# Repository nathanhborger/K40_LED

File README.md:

# K40_LED
LED Ring Origin Light for K40 Laser.
This device was designed with the intention to provide a solution to the K40's lack of origin detection/positioning.
Placed at the back of the laser, and reflected through two mirrors, the light will shine on the working peice, making a very distinct appearance which simplifies and enables the user to identify the exact locatin of the laser head.

## Schematic

## PCB Layout

## PCB

## Parts List
| QTY | PART | NOTES |
|:---:|:----:|:-----:|
|8|LED XLAMP COOL WHITE 5000K 2SMD|https://cree-led.com/media/documents/XLampMX3.pdf|
|13|RES 13 OHM 1% 1/8W 0805||
|4|IC LED DRIVER LIN 1.5A 8SOPWRPAD|https://www.ti.com/general/docs/suppproductinfo.tsp?distId=10&gotoUrl=https%3A%2F%2Fwww.ti.com%2Flit%2Fgpn%2Flm3466|
|1|LED DRIVER CC BUCK 2-52V 350MA|https://www.meanwellusa.com/upload/pdf/LDD-H/LDD-H-spec.pdf|
|4|RES SMD 1 OHM 1% 1/8W 0805||
|4|CAP CER 0.011UF 50V C0G/NP0 0805	||
|5|CAP CER 1UF 16V X7R 0805||
|1|RES SMD 51.1 OHM 1% 1/8W 0805||

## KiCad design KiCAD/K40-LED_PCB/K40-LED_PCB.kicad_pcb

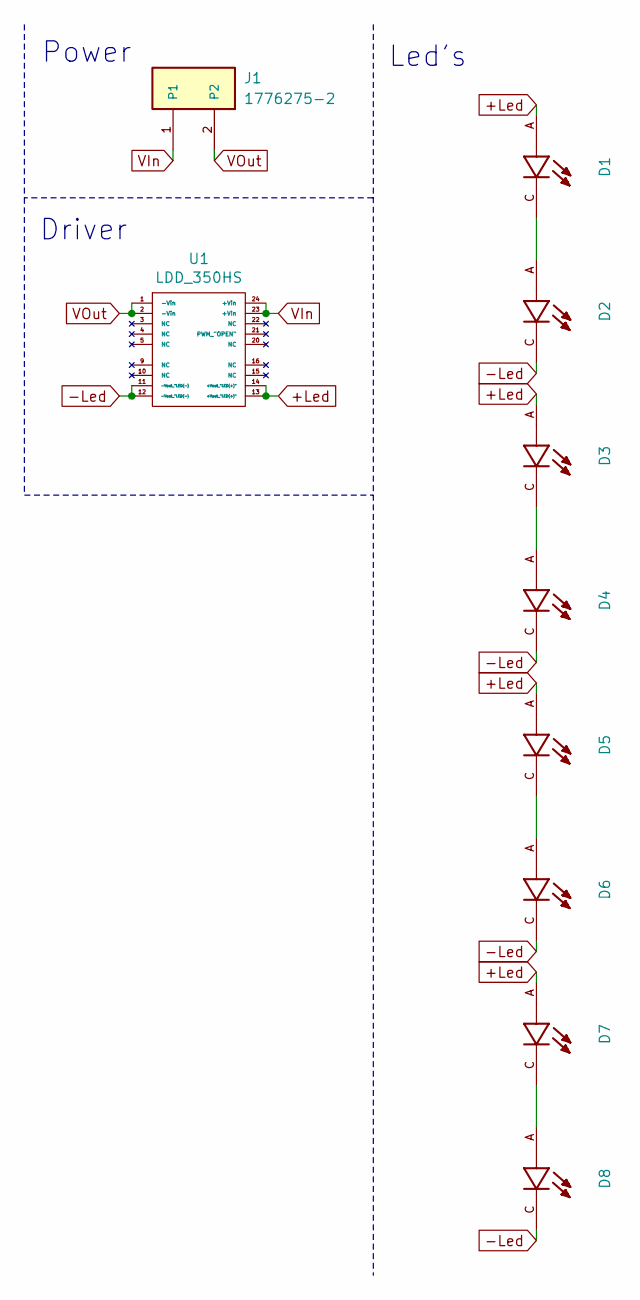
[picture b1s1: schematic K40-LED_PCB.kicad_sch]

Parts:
D1: Cree_MX3AWT-A1-R250-000BE3
D2, D3, D4, D5, D6, D7, D8: LTST-C190KGKT; Cree_MX3AWT-A1-R250-000BE3
J1: 1776275-2; TE_1776275-2; VOLTAGE_RATING_AC 250V; PART_DESCRIPTION TERM BLOCK 2POS SIDE ENT 3.5MM
U1: LDD_350HS; LDD-350HS

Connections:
+Led: D1.A, D3.A, D5.A, D7.A, U1.13 (+Vout_"LED(+)"), U1.14 (+Vout_"LED(+)")
-Led: D2.C, D4.C, D6.C, D8.C, U1.11 (-Vout_"LED(-)), U1.12 (-Vout_"LED(-))
unnamed: D1.C, D2.A
unnamed: D3.C, D4.A
unnamed: D5.C, D6.A
unnamed: D7.C, D8.A
VIn: J1.1, U1.23 (+Vin), U1.24 (+Vin); also elsewhere on the board
VOut: J1.2, U1.1 (-Vin), U1.2 (-Vin)

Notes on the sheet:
Power
Led's
Driver

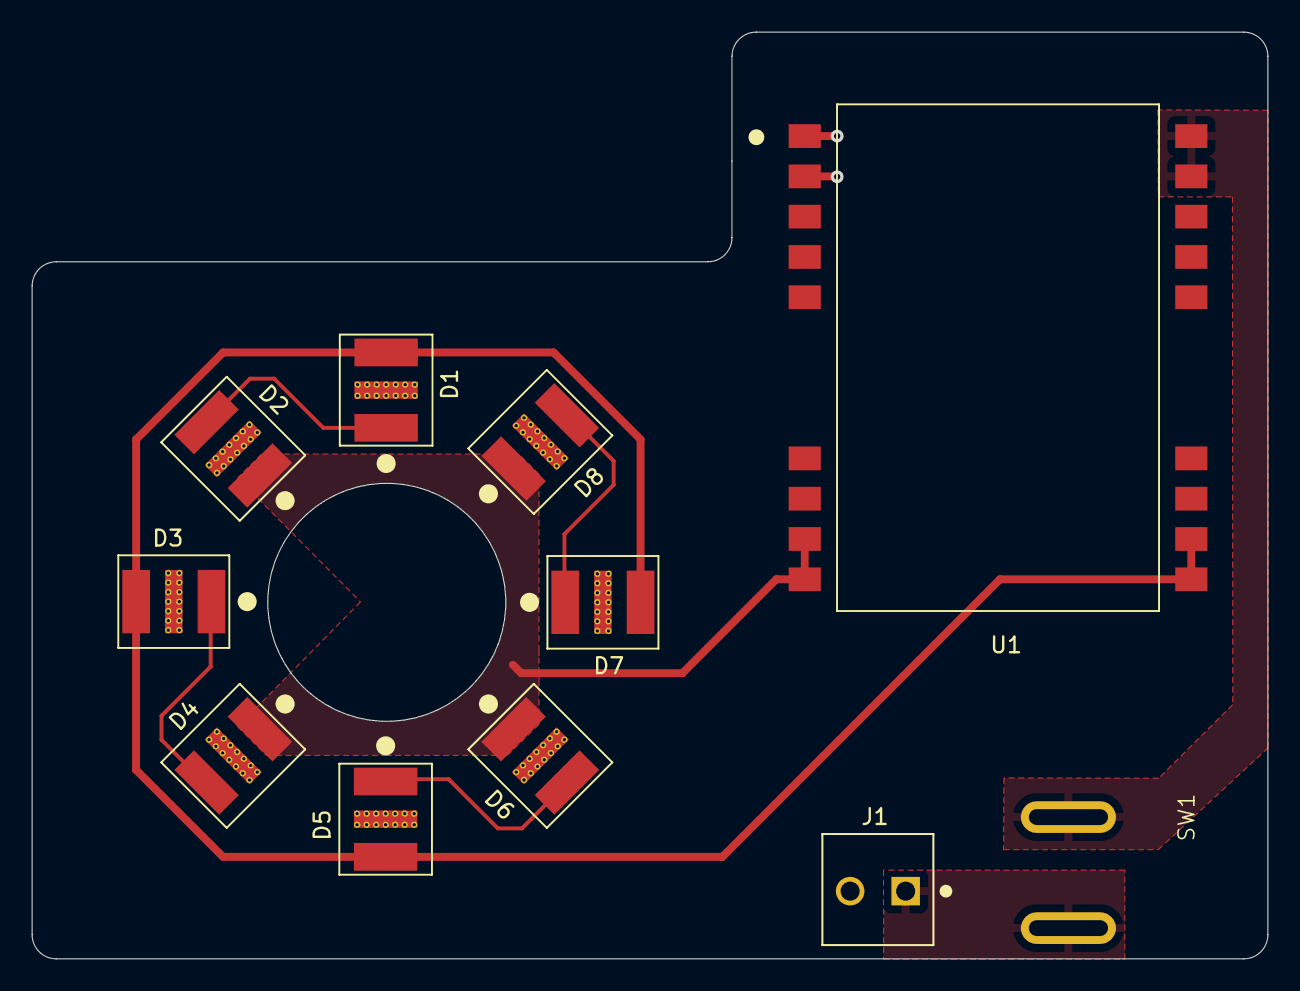
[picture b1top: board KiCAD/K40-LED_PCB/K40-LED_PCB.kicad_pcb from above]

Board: 2 copper layers, 77.9 x 58.4 mm, 11 parts (0 on the bottom side), 8 nets.

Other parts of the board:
SW1: SW_SPST; RA1113112R

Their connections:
VIn: SW1.1 (A), SW1.2 (B); also elsewhere on the board

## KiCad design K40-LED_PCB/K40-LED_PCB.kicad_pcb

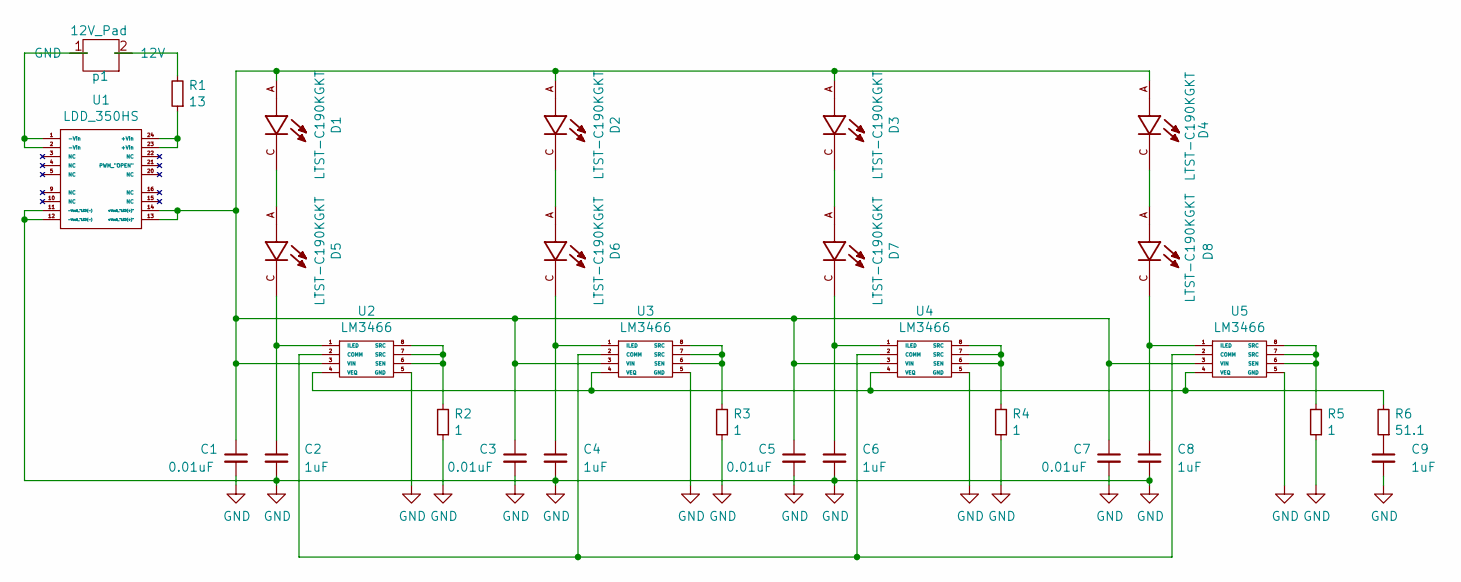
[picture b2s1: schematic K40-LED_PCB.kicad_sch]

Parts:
C1, C3, C5, C7: 0.01uF; C_0805_2012Metric
C2, C4, C6, C8, C9: 1uF; C_0805_2012Metric
D1, D2, D3, D4, D5, D6, D7, D8: LTST-C190KGKT; Cree_MX3AWT-A1-R250-000BE3
R1: 13; R_0805_2012Metric
R2, R3, R4, R5: 1; R_0805_2012Metric
R6: 51.1; R_0805_2012Metric
U1: LDD_350HS; LDD-350HS
U2, U3, U4, U5: LM3466; NOPB
p1: 12V_Pad; 12V_Through_Hole

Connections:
GND: C1.2, C2.2, C3.2, C4.2, C5.2, C6.2, C7.2, C8.2, C9.2, D1.65, D2.65, D3.65, D4.65, D5.65, D6.65, D7.65, D8.65, R2.1, R3.1, R4.1, R5.1, U1.11 (-Vout_"LED(-)), U1.12 (-Vout_"LED(-)), U2.5 (GND), U2.9, U3.5 (GND), U3.9, U4.5 (GND), U4.9, U5.5 (GND), U5.9
unnamed: C1.1, C3.1, C5.1, C7.1, D1.A, D2.A, D3.A, D4.A, U1.13 (+Vout_"LED(+)"), U1.14 (+Vout_"LED(+)"), U2.3 (VIN), U3.3 (VIN), U4.3 (VIN), U5.3 (VIN)
unnamed: C2.1, D5.C, U2.1 (ILED)
unnamed: C4.1, D6.C, U3.1 (ILED)
unnamed: C6.1, D7.C, U4.1 (ILED)
unnamed: C8.1, D8.C, U5.1 (ILED)
unnamed: C9.1, R6.1
unnamed: D1.C, D5.A
unnamed: D2.C, D6.A
unnamed: D3.C, D7.A
unnamed: D4.C, D8.A
unnamed: R1.1, U1.23 (+Vin), U1.24 (+Vin)
unnamed: R1.2, p1.2 (12V)
unnamed: R2.2, U2.6 (SEN), U2.7 (SRC), U2.8 (SRC)
unnamed: R3.2, U3.6 (SEN), U3.7 (SRC), U3.8 (SRC)
unnamed: R4.2, U4.6 (SEN), U4.7 (SRC), U4.8 (SRC)
unnamed: R5.2, U5.6 (SEN), U5.7 (SRC), U5.8 (SRC)
unnamed: R6.2, U2.4 (VEQ), U3.4 (VEQ), U4.4 (VEQ), U5.4 (VEQ)
unnamed: U1.1 (-Vin), U1.2 (-Vin), p1.1 (GND)
unnamed: U2.2 (COMM), U3.2 (COMM), U4.2 (COMM), U5.2 (COMM)

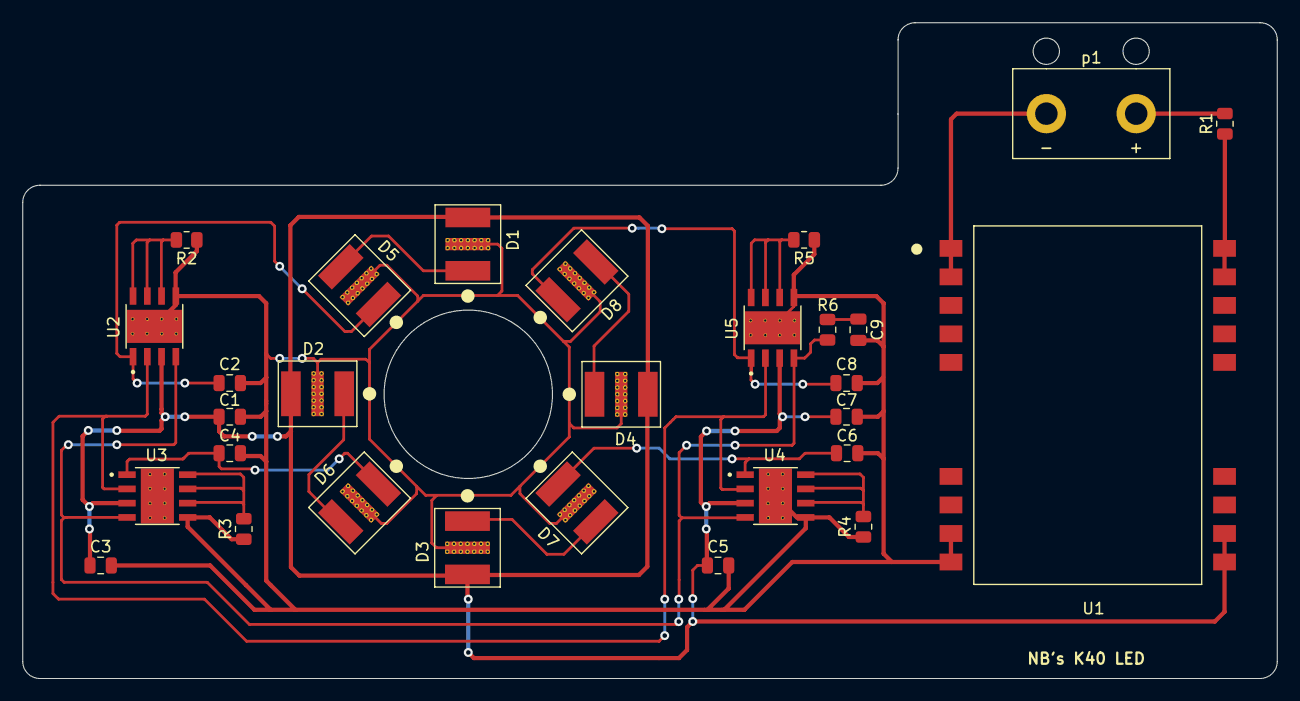
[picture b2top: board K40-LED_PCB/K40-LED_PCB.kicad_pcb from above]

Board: 2 copper layers, 111.7 x 58.4 mm, 29 parts (0 on the bottom side), 20 nets.

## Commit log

2021-07-02 Folders Added
2021-07-02 AutoSave
2021-07-02 Symbols
2021-07-02 Schmatic Update
2021-07-03 Footprint_Update
2021-07-03 Assign_Footprints
2021-07-03 General_layout
2021-07-03 PCB_Update
2021-07-03 PCb_Complete
2021-07-03 Added Gerber
2021-07-03 Added_Gerbers
2021-07-03 File_Changes
2021-07-13 Added Step files
2021-07-14 Added new led footprint
2021-07-14 Connect symbol to new footprint
2021-07-14 Trace deletion
2021-07-15 more footprints
2021-07-15 Symbol Changes
2021-07-15 More Footprint updates
2021-07-17 Footprint updates
2021-07-17 updated more footprints
2021-07-17 removed old footprint associations
2021-07-18 New Symbol for LDD-350HS
2021-07-18 Major PCB Changes
2021-07-18 PCB_Changes + footprints
2021-07-18 PCB_Updates
2021-07-18 PCB_Circular_Formation
2021-07-18 More circular changes correct
2021-07-18 PCB Cathode traces
2021-07-18 Cont Traces
2021-07-18 More_PCB Updates LM3466 movementr
2021-07-18 More PCB Updates
2021-07-18 Updated more PCB
2021-07-18 Updated PCB Again
2021-07-22 PCB_Updates_Chaned_LM_Layout
2021-07-22 Finished_PCB
2021-08-07 Lots of updates on the K40 LED
2021-08-07 Thermal Reliefs updated
2021-08-07 More Thermal Pad Updates
2021-08-08 More Thermal Upgrades and Progression
2021-08-08 D8 Thermal Updates
2021-08-08 D8 Thermal Upgrades
2021-08-08 Continued Upgrades to Thermal Pads
2021-08-08 Upgraded Thermal Relief
2021-08-08 Grounding Thermal Relief Pads
2021-08-08 Continued Updates On Thermal
2021-08-08 Thermals Completed to Ground
2021-08-17 updated k40 led
2022-01-11 Added a Parts List
2022-01-11 Parts List Edit
2022-01-11 Adding Parts
2022-01-11 Finished Parts List
2022-01-11 Adding Images
2022-01-11 Added More images
2022-01-11 Added design intentions
2022-01-12 Added Physical Circuit Image
2023-12-10 Initial Upgrades to recent KiCAD
2023-12-10 Initial Restructure
2023-12-10 Working on PCB - Schematic finalized
2024-01-06 SPST switch footprint completed & finished routing
